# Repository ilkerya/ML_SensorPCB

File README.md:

# ML_SensorPCB
Add On PCB for Arduino Mega 256 designed with Kicad,
Sensor DataLogger for Enose,
Sizes 101.64 mm x 53.35 mm

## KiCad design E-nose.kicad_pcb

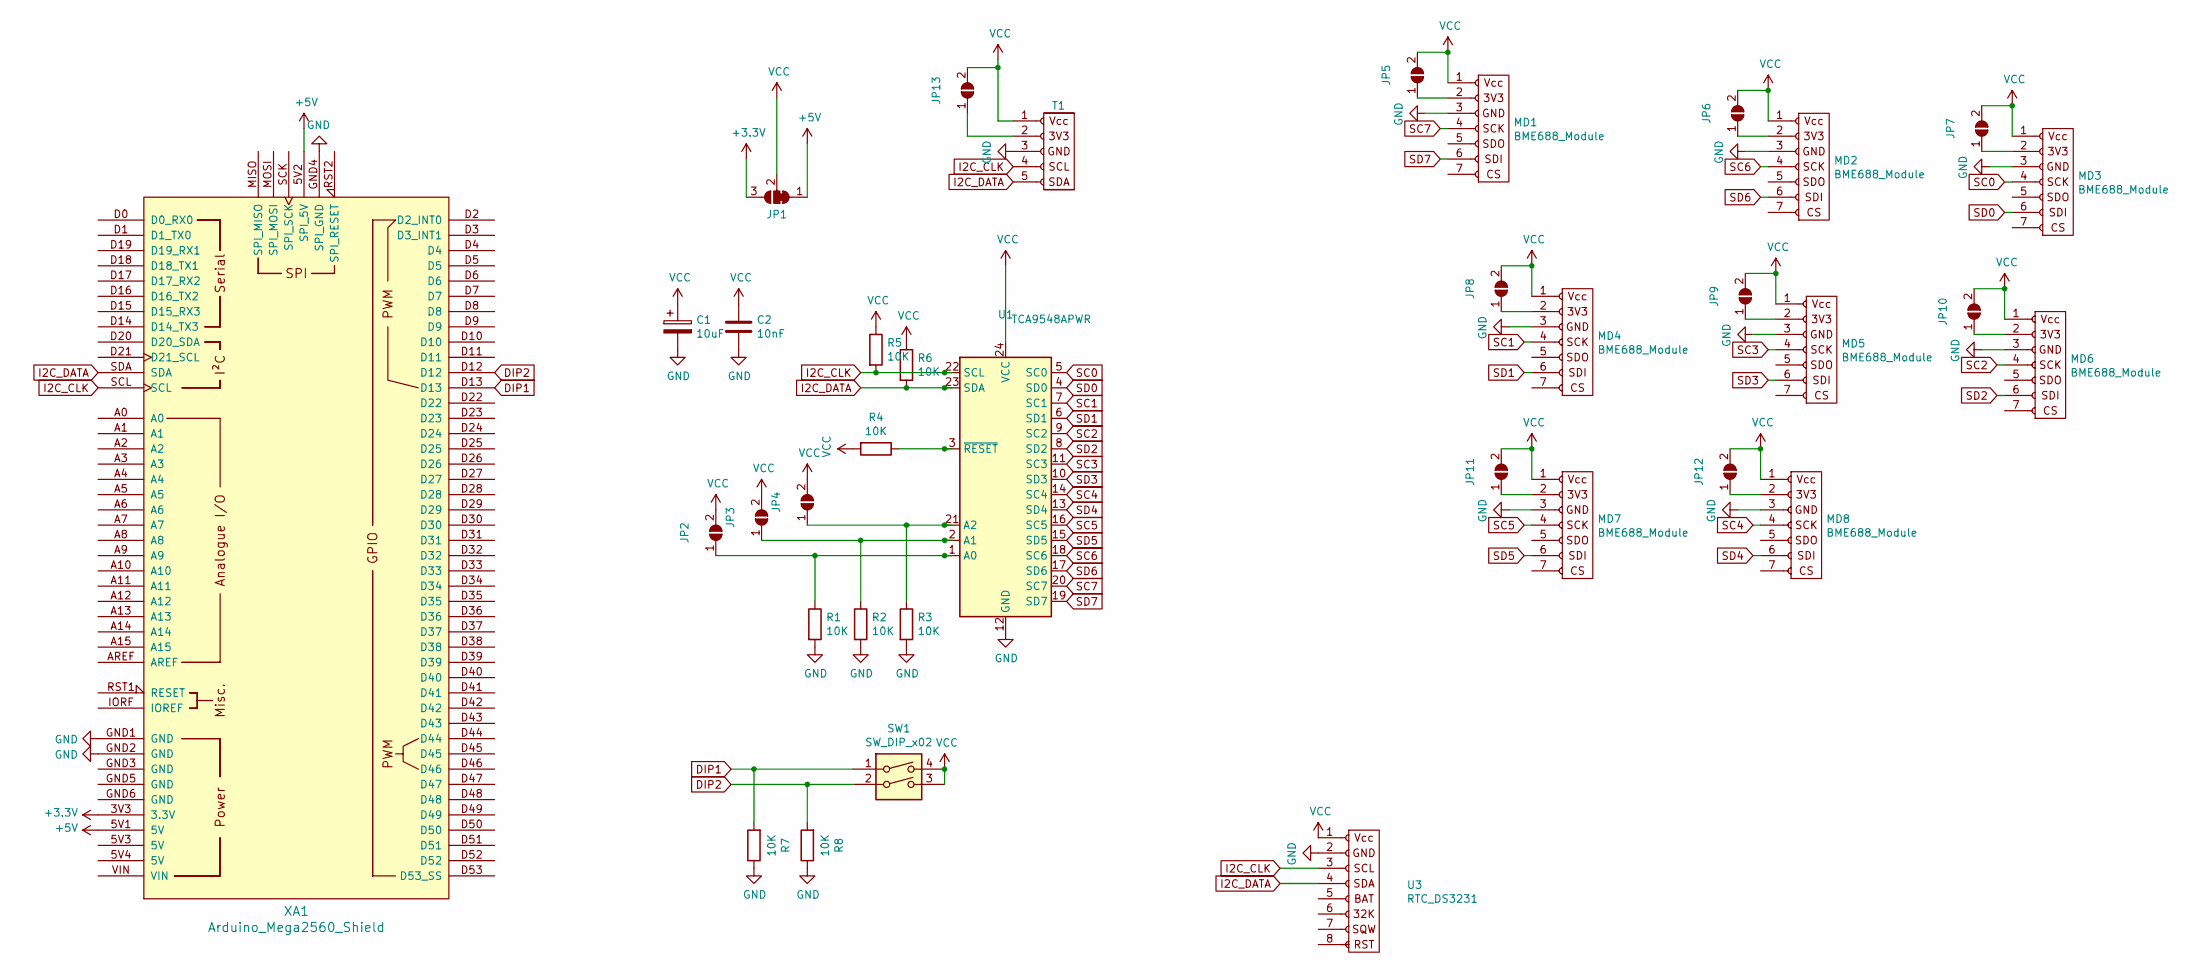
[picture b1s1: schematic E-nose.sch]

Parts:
C1: 10uF; CP_Radial_D5.0mm_P2.00mm
C2: 10nF; C_0805_2012Metric_Pad1.18x1.45mm_HandSolder
JP1: SolderJumper_3_Bridged12; SolderJumper-3_P1.3mm_Bridged12_Pad1.0x1.5mm
JP2, JP3, JP4, JP5, JP6, JP7, JP8, JP9, JP10, JP11, JP12, JP13: SolderJumper_2_Open; SolderJumper-2_P1.3mm_Open_RoundedPad1.0x1.5mm
MD1, MD2, MD3, MD4, MD5, MD6, MD7, MD8: BME688_Module; BME688
R1, R2, R3, R4, R5, R6, R7, R8: 10K; R_0805_2012Metric_Pad1.20x1.40mm_HandSolder
SW1: SW_DIP_x02; SW_DIP_SPSTx02_Slide_6.7x6.64mm_W7.62mm_P2.54mm_LowProfile
T1: Temp_si072
U1: TCA9548APWR; TSSOP-24_4.4x7.8mm_P0.65mm
U3: RTC_DS3231
XA1: Arduino_Mega2560_Shield

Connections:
+3V3: JP1.3 (B), XA1.3V3 (3.3V)
+5V: JP1.1 (A), XA1.5V1 (5V), XA1.5V2 (SPI_5V)
DIP1: R7.2, SW1.1, XA1.D13
DIP2: R8.2, SW1.2, XA1.D12
GND: C1.2, C2.2, MD1.3, MD2.3, MD3.3, MD4.3, MD5.3, MD6.3, MD7.3, MD8.3, R1.2, R2.2, R3.2, R7.1, R8.1, T1.3, U1.12 (GND), U3.2 (3V3), XA1.GND1 (GND), XA1.GND2 (GND), XA1.GND4 (SPI_GND)
I2C_CLK: R5.2, T1.4, U1.22 (SCL), U3.3, XA1.SCL
I2C_DATA: R6.2, T1.5, U1.23 (SDA), U3.4, XA1.SDA
unnamed: JP2.1 (A), R1.1, U1.1 (A0)
unnamed: JP3.1 (A), R2.1, U1.2 (A1)
unnamed: JP4.1 (A), R3.1, U1.21 (A2)
unnamed: JP5.1 (A), MD1.2 (3V3)
unnamed: JP6.1 (A), MD2.2 (3V3)
unnamed: JP7.1 (A), MD3.2 (3V3)
unnamed: JP8.1 (A), MD4.2 (3V3)
unnamed: JP9.1 (A), MD5.2 (3V3)
unnamed: JP10.1 (A), MD6.2 (3V3)
unnamed: JP11.1 (A), MD7.2 (3V3)
unnamed: JP12.1 (A), MD8.2 (3V3)
unnamed: JP13.1 (A), T1.2
unnamed: R4.1, U1.3 (~RESET)
SC0: MD3.4, U1.5 (SC0)
SC1: MD4.4, U1.7 (SC1)
SC2: MD6.4, U1.9 (SC2)
SC3: MD5.4, U1.11 (SC3)
SC4: MD8.4, U1.14 (SC4)
SC5: MD7.4, U1.16 (SC5)
SC6: MD2.4, U1.18 (SC6)
SC7: MD1.4, U1.20 (SC7)
SD0: MD3.6, U1.4 (SD0)
SD1: MD4.6, U1.6 (SD1)
SD2: MD6.6, U1.8 (SD2)
SD3: MD5.6, U1.10 (SD3)
SD4: MD8.6, U1.13 (SD4)
SD5: MD7.6, U1.15 (SD5)
SD6: MD2.6, U1.17 (SD6)
SD7: MD1.6, U1.19 (SD7)
VCC: C1.1, C2.1, JP1.2 (C), JP2.2 (B), JP3.2 (B), JP4.2 (B), JP5.2 (B), JP6.2 (B), JP7.2 (B), JP8.2 (B), JP9.2 (B), JP10.2 (B), JP11.2 (B), JP12.2 (B), JP13.2 (B), MD1.1 (Vcc), MD2.1 (Vcc), MD3.1 (Vcc), MD4.1 (Vcc), MD5.1 (Vcc), MD6.1 (Vcc), MD7.1 (Vcc), MD8.1 (Vcc), R4.2, R5.1, R6.1, SW1.3, SW1.4, T1.1, U1.24 (VCC), U3.1 (Vcc)

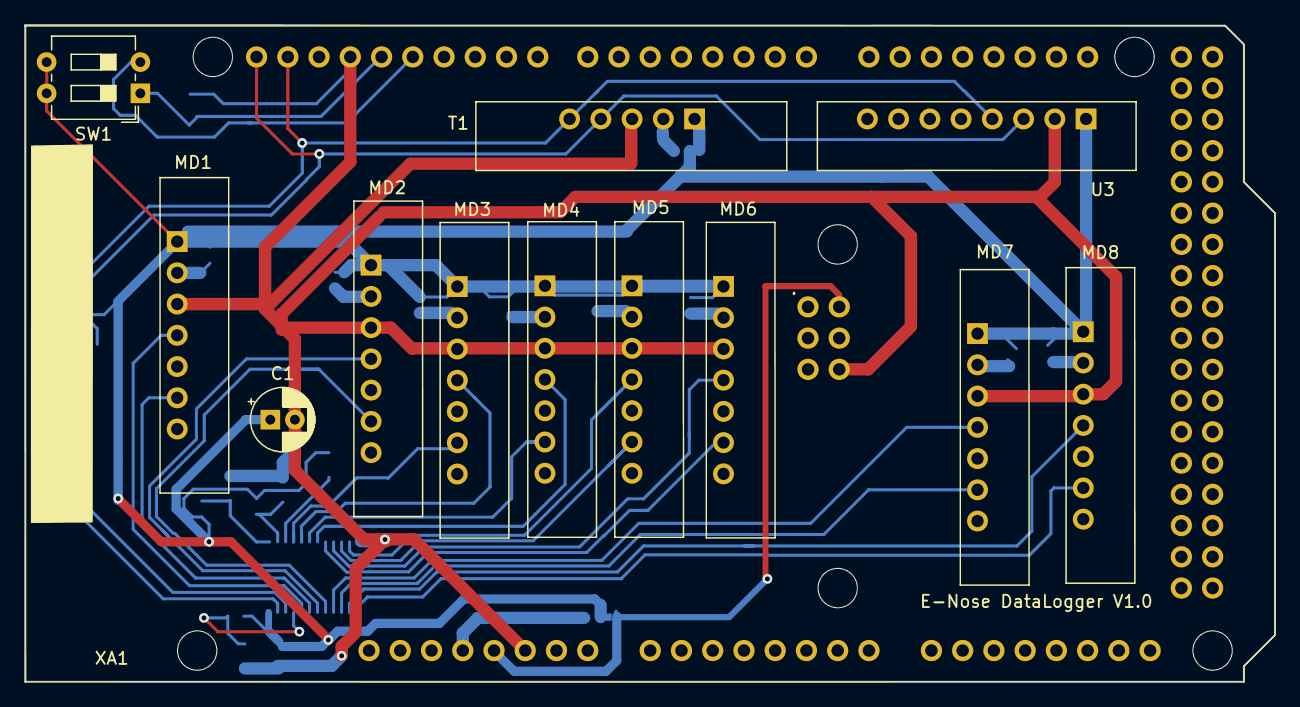
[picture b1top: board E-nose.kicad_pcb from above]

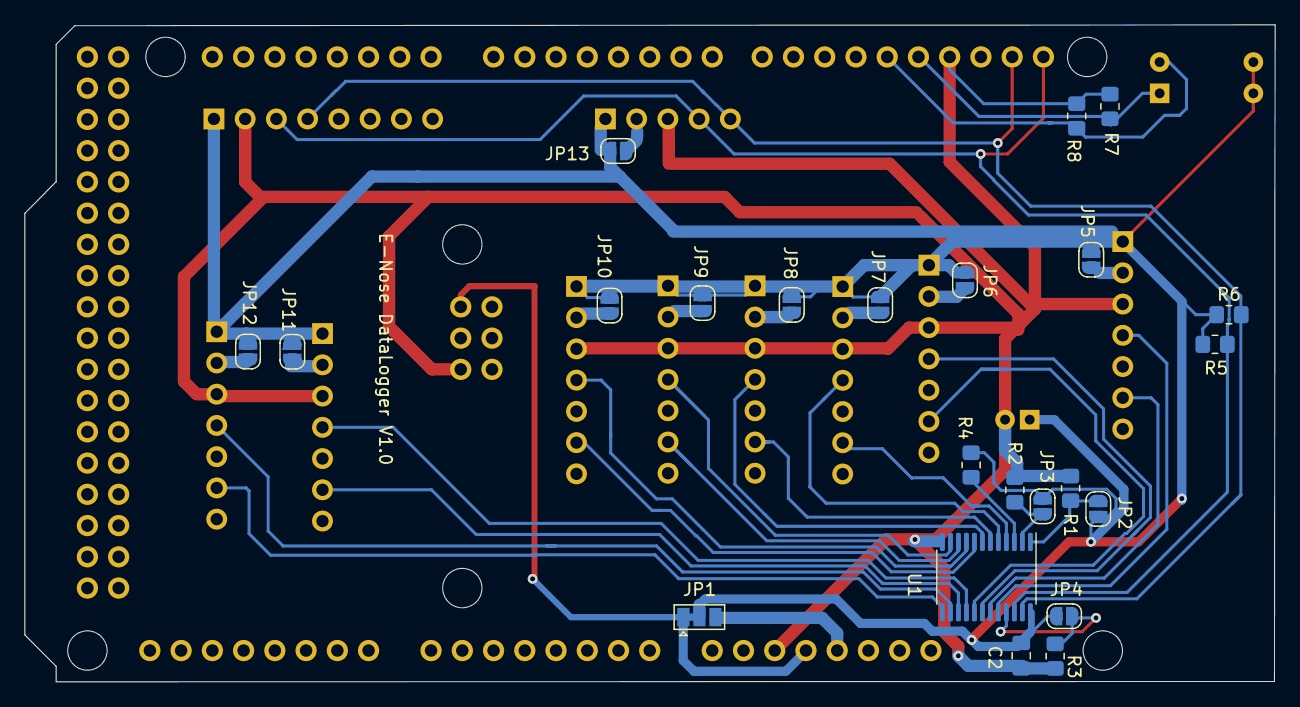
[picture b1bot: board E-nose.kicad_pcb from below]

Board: 2 copper layers, 101.6 x 53.4 mm, 36 parts (23 on the bottom side), 37 nets.

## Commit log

2022-02-23 Final with Gerbers
2022-02-23 Final with 3D view
2022-02-27 Dip switch add
